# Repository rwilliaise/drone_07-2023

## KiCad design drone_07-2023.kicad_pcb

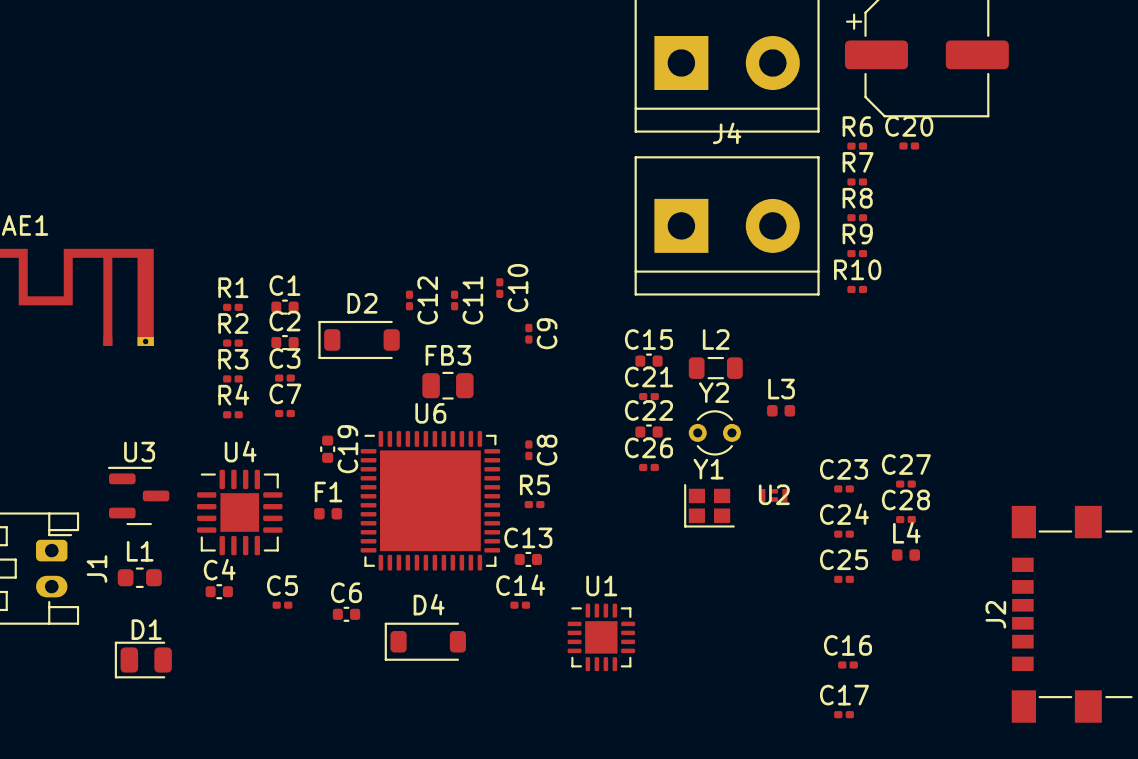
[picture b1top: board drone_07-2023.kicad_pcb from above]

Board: 2 copper layers, 59 parts (0 on the bottom side), 36 nets, no tracks yet.

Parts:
AE1: 2.4GHz; Texas_SWRA117D_2.4GHz_Left
C1, C2, C13, C15, C19: 4.7uF; C_0402_1005Metric
C3, C5, C8, C9, C10, C11, C12, C14, C26: 100nF; C_0201_0603Metric
C4: 10uF; C_0402_1005Metric
C6, C22: 1uF; C_0402_1005Metric
C7, C20, C21: 10nF; C_0201_0603Metric
C16: 22nF; C_0201_0603Metric
C17: 2.2uF; C_0201_0603Metric
C18: 22uF; CP_Elec_6.3x5.4
C23: 100pF; C_0201_0603Metric
C24, C25: 10pF; C_0201_0603Metric
C27: 0.3pF; C_0201_0603Metric
C28: 0.8pF; C_0201_0603Metric
D1: 572nm; LED_0805_2012Metric
D2, D4: 40V @ 300mA; D_SOD-123
F1: 500mA; Fuse_0402_1005Metric
FB3: 120 @ 100 mHz; Fuse_0805_2012Metric
J1: JST_PH; JST_PH_S2B-PH-K_1x02_P2.00mm_Horizontal
J2: USB_C_Receptacle_PowerOnly_6P; USB_C_Receptacle_GCT_USB4135-GF-A_6P_TopMnt_Horizontal
J3: Brushed DC Northeast; TerminalBlock_bornier-2_P5.08mm
J4: Brushed DC Southeast; TerminalBlock_bornier-2_P5.08mm
L1: 39nH; L_0603_1608Metric
L2: 10uH; L_0805_2012Metric
L3: 10nH; L_0402_1005Metric
L4: 2.7nH; L_0402_1005Metric
R1, R2: 5.1k; R_0201_0603Metric
R3, R4: 97.6k; R_0201_0603Metric
R5: 150; R_0201_0603Metric
R6: 47k; R_0201_0603Metric
R7: 1k; R_0201_0603Metric
R8, R9, R10: 330m; R_0201_0603Metric
U1: STSPIN240; VQFN-16-1EP_3x3mm_P0.5mm_EP1.8x1.8mm
U2: DLF162500LT-5028A1; DLF-4_1P6X0P8
U3: MCP1754S-3302xCB; SOT-23
U4: LTC4055; QFN-16-1EP_4x4mm_P0.65mm_EP2.15x2.15mm
U6: STM32WB35C_C-E_UxA; QFN-48-1EP_7x7mm_P0.5mm_EP5.6x5.6mm
Y1: 32MHz; Crystal_SMD_2016-4Pin_2.0x1.6mm
Y2: 32kHz; Crystal_Round_D2.0mm_Vertical

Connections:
+BATT: J1.1, U4.2 (BAT)
-BATT: AE1.1 (FEED), C1.2, C2.2, C3.2, C4.2, C5.2, C6.2, C7.2, C8.2, C9.2, C10.2, C11.2, C12.2, C13.1, C14.1, C15.2, C16.2, C17.2, C18.1, C19.2, C20.1, C21.2, C22.1, C23.2, C24.2, C25.2, C26.2, C27.2, C28.2, J1.2, J2.A12 (GND), J2.B12 (GND), R1.2, R2.2, R3.1, R4.2, R6.2, R8.2, R9.1, R10.2, U1.7 (GND), U1.17 (EPAD), U2.2 (GND), U2.4 (GND), U3.1 (GND), U4.5 (WALL), U4.6 (SHDN), U4.10 (GND), U4.16 (NTC), U4.17 (GND), U6.22 (VSSRF), U6.32 (VSSSMPS), U6.49 (VSS)
unnamed: AE1.2 (PCB_Trace), U2.3 (OUT)
unnamed: C16.1, R7.2
unnamed: D1.2 (A), R5.1
unnamed: D1.1 (K), U4.14 (~CHRG)
unnamed: D2.1 (K), F1.1
unnamed: C14.2, D4.2 (A), U6.7 (NRST)
unnamed: F1.2, FB3.1
unnamed: J2.A5 (CC1), R2.1
unnamed: J2.B5 (CC2), R1.1
unnamed: J3.1, U1.3 (OUTA1)
unnamed: J3.2, U1.5 (OUTA2)
unnamed: J4.1, U1.10 (OUTB1)
unnamed: J4.2, U1.8 (OUTB2)
unnamed: L2.2, L3.1
unnamed: C20.2, R10.1, U1.11 (REF)
unnamed: R8.1, U1.4 (SENSEA)
unnamed: R9.2, U1.9 (SENSEB)
unnamed: R6.1, R7.1, U1.12 (TOFF)
unnamed: C27.1, L4.2, U2.1 (IN)
unnamed: C1.1, FB3.2, U3.3 (VI)
unnamed: R3.2, U4.9 (CLPROG)
unnamed: R4.1, U4.11 (PROG)
unnamed: C3.1, U4.12 (TIMER)
unnamed: U6.25 (OSC_IN), Y1.2
unnamed: U6.24 (OSC_OUT), Y1.1
unnamed: C25.1, U6.2 (PC14), Y2.2
unnamed: C24.1, U6.3 (PC15), Y2.1
RF1: C28.1, L4.1, U6.21 (RF1)
VBUS: J2.A9 (VBUS), J2.B9 (VBUS), U4.1 (IN), U4.4 (IN)
VCC: C4.1, D2.2 (A), R5.2, U4.3 (OUT), U4.8 (HPWR)
VDDA: C6.1, C7.1, C21.1, C22.2, L1.2, U6.8 (VDDA)
VDDRF: C2.1, C5.1, C8.1, C9.1, C10.1, C11.1, C12.1, C15.1, C17.1, C18.2, C19.1, C23.1, C26.1, L1.1, U1.6 (VS), U3.2 (VO), U6.1 (VBAT), U6.20 (VDD), U6.23 (VDDRF), U6.34 (VDDSMPS), U6.35 (VDD), U6.40 (VDDUSB), U6.48 (VDD)
VFBSMPS: C13.2, L3.2, U6.31 (VFBSMPS)
VLXSMPS: L2.1, U6.33 (VLXSMPS)

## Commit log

2024-03-14 Catalogued in raja.rocks
2024-03-14 Create LICENSE
